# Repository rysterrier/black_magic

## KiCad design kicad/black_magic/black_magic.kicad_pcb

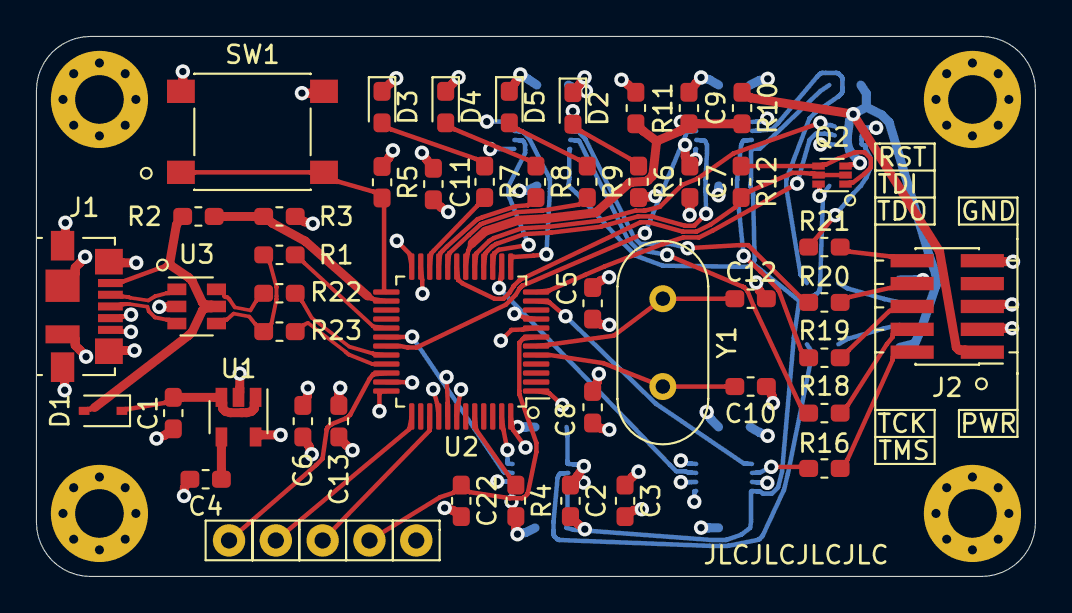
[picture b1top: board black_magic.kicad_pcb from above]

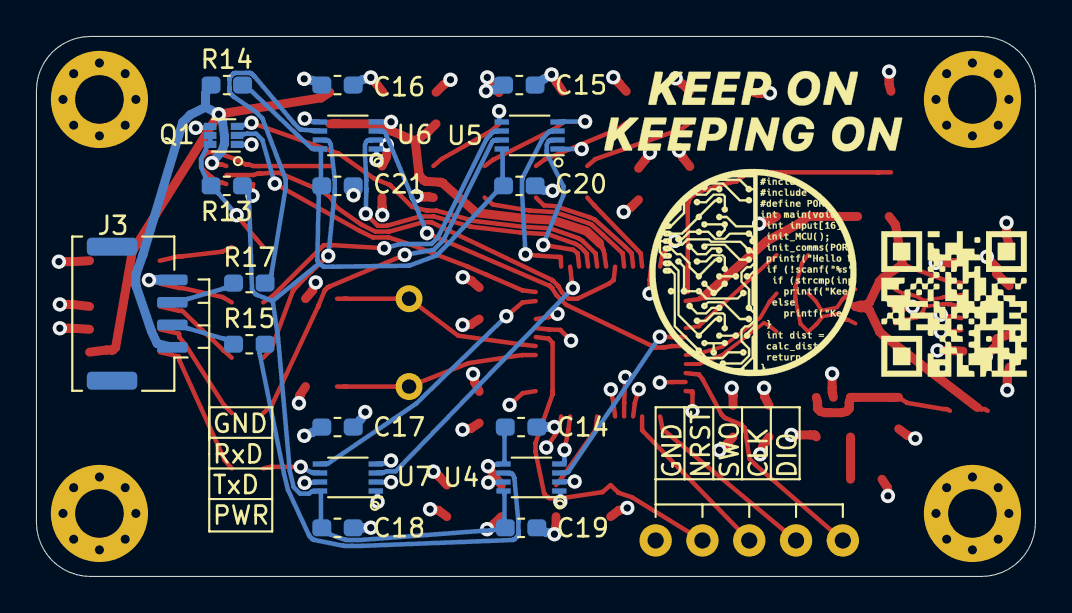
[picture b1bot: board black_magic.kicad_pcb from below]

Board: 4 copper layers, 55.5 x 30.0 mm, 75 parts (20 on the bottom side), 56 nets.

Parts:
C1, C2, C6: 4.7uF; C_0603_1608Metric_Pad1.05x0.95mm_HandSolder
C3, C7, C8, C9, C11, C13, C14, C15, C16, C17, C18, C19, C20, C21, C22: 100nF; C_0603_1608Metric_Pad1.05x0.95mm_HandSolder
C4: 10nF; C_0603_1608Metric_Pad1.05x0.95mm_HandSolder
C5: 1uF; C_0603_1608Metric_Pad1.05x0.95mm_HandSolder
C10, C12: 22pF; C_0603_1608Metric_Pad1.05x0.95mm_HandSolder
D1: BAT60A; D_SOD-323
D2: GREEN; LED_0603_1608Metric_Pad1.05x0.95mm_HandSolder
D3: RED; LED_0603_1608Metric_Pad1.05x0.95mm_HandSolder
D4: ORANGE; LED_0603_1608Metric_Pad1.05x0.95mm_HandSolder
D5: YELLOW; LED_0603_1608Metric_Pad1.05x0.95mm_HandSolder
H1, H2, H3, H4: MountingHole; MountingHole_2.7mm_M2.5_Pad_Via
J1: USB_B_Micro; USB_Micro-B_Molex_47346-0001
J2: JTAG-10; PinHeader_2x05_P1.27mm_Vertical_SMD
J3: Conn_01x04; Molex_CLIK-Mate_502382-0470_1x04-1MP_P1.25mm_Vertical
LOGO1: Fiducial; black_magic
LOGO2: Fiducial; keep_on
P14, P15, P16, P17, P18: Conn_01x01; Pin_D0.9mm_L10.0mm_W2.4mm_FlatFork
Q1: DMG1024UV; SOT-563
Q2: DMG1023UV; SOT-563
R1: 1k5; R_0603_1608Metric_Pad1.05x0.95mm_HandSolder
R2, R10: 4.7k; R_0603_1608Metric_Pad1.05x0.95mm_HandSolder
R3, R4, R5, R11, R12, R13: 10k; R_0603_1608Metric_Pad1.05x0.95mm_HandSolder
R6, R7, R8, R9: 330; R_0603_1608Metric_Pad1.05x0.95mm_HandSolder
R14, R15, R16, R17, R18, R19, R20, R21: 100; R_0603_1608Metric_Pad1.05x0.95mm_HandSolder
R22, R23: 22; R_0603_1608Metric_Pad1.05x0.95mm_HandSolder
SW1: SW_Push; SW_Push_1P1T_NO_6x6mm_H9.5mm
U1: LP2985-3.3; SOT-23-5
U2: STM32F103CBTx; LQFP-48_7x7mm_P0.5mm
U3: USBLC6-2SC6; SOT-23-6
U4, U5, U6, U7: 74LVC2T45DC; VSSOP-8_2.3x2mm_P0.5mm
Y1: 8MHz; Crystal_HC49-U_Vertical

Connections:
+3V3: C2.1, C3.1, C5.1, C6.1, C7.1, C8.1, C11.1, C13.1, C14.2, C15.2, C16.2, C17.2, Q2.6, R5.1, R6.2, U1.5, U2.1, U2.9, U2.24, U2.36, U2.40, U2.41, U2.42, U2.48, U4.1, U4.5, U5.1, U5.5, U6.1, U7.1
+5V: D1.2, J1.1, R2.1, U3.5
/RST: J2.10, R21.2
/RXD: J3.3, R17.1
/TCK: J2.4, R18.1
/TDI: J2.8, R20.2
/TDO: J2.6, R19.1
/TMS: J2.2, R16.1
/TXD: J3.2, R15.1
/USB+: R1.2, R23.2, U3.4
/USB-: R22.1, U3.6
BOOT0: R4.1, U2.44
BTN: R5.2, SW1.1, U2.25
D+: J1.3, U3.3
D-: J1.2, U3.1
GND: C1.2, C2.2, C3.2, C4.2, C5.2, C6.2, C7.2, C8.2, C9.2, C10.2, C11.2, C12.2, C13.2, C14.1, C15.1, C16.1, C17.1, C18.1, C19.1, C20.1, C21.1, C22.2, D2.1, D3.1, D4.1, D5.1, J1.4, J1.5, J1.6, J2.3, J2.5, J2.9, J3.4, P18.1, Q1.1, Q1.4, R3.2, R4.2, R11.2, SW1.2, U1.2, U2.8, U2.23, U2.35, U2.47, U3.2, U4.2, U4.4, U4.7, U5.4, U6.4, U6.5, U7.2, U7.4, U7.7
HSE_IN: C10.1, U2.5, Y1.1
HSE_OUT: C12.1, U2.6, Y1.2
LED1: R9.2, U2.20
LED2: R8.2, U2.21
LED3: R7.2, U2.22
NRST: C22.1, P14.1, U2.7
unnamed: C1.1, D1.1, U1.1, U1.3
unnamed: C4.1, U1.4
unnamed: D2.2, R6.1
unnamed: D3.2, R7.1
unnamed: D4.2, R8.1
unnamed: D5.2, R9.1
unnamed: Q2.1, Q2.4, R12.1
PWR_BR: Q2.2, Q2.5, R12.2, U2.19
SWCLK: P16.1, U2.37
SWDIO: P17.1, U2.34
TPWR: J2.1, J3.1, Q2.3, R10.1, R14.1
TRACE_SWO: P15.1, U2.39
T_PWR: C9.1, R10.2, R11.1, U2.18
USB_D+: R23.1, U2.33
USB_D-: R22.2, U2.32
USB_REN: R1.1, U2.29
VBUS: R2.2, R3.1, U2.26
iRST: Q1.2, U2.12
iRST_SENCE: Q1.3, U2.17
iRXD: U2.31, U6.3
iTCK: U2.15, U5.2
iTDI: U2.13, U5.3
iTDO: U2.16, U6.2
iTMS: U2.14, U7.3
iTMS_DIR: U2.11, U7.5
iTXD: U2.30, U4.3
xRST: Q1.5, Q1.6, R13.2, R21.1
xRXD: R17.2, U6.6
xTCK: R18.2, U5.7
xTDI: R20.1, U5.6
xTDO: R19.2, U6.7
xTMS: R16.2, U7.6
xTPWR: C18.2, C19.2, C20.2, C21.2, R13.1, R14.2, U4.8, U5.8, U6.8, U7.8
xTXD: R15.2, U4.6

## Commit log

2020-05-30 Added PCB + Schemtaics
    Added PCB and Sch files
